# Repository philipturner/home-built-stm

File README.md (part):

## Members
Philip Turner, Nanoscience Student (2025)
philipturner@vt.edu

## Project Overview

> _Complexity is the nemesis of progress._

STM with no nonlinearities in the relationship between piezo voltage and position.

Presentation:
- [Video (YouTube)](https://www.youtube.com/watch?v=1APURT2G7bo)
- [Slides (PDF)](./Documentation/Presentation/Final%20Presentation.pdf)

Table of Contents:
- Journal Entries (Planning Stage)
  - [Progress (Jan 2025)](#progress-jan-2025)
  - [High-Level Overview](#high-level-overview)
  - [Lithium Niobate](#lithium-niobate)
  - [Finite Element Modeling](#finite-element-modeling)
  - [Chips](#chips)
  - [Update (February 22, 2025)](#update-february-22-2025)
  - [First Draft of TIA Subsystem](#first-draft-of-tia-subsystem)
  - [Bypassing vs. Decoupling Capacitors](#bypassing-vs-decoupling-capacitors)
- Journal Entries (Theoretical Stage)
  - [March 6, 2025](#march-6-2025)
  - [March 15, 2025](#march-15-2025)
  - [March 18, 2025](#march-18-2025)
  - [March 19, 2025](#march-19-2025)
  - [March 20, 2025](#march-20-2025)
  - [March 21, 2025](#march-21-2025)
  - [March 22, 2025](#march-22-2025)
  - [March 23, 2025](#march-23-2025)
  - [March 25, 2025](#march-25-2025)
  - [March 28, 2025](#march-28-2025)
  - [March 29, 2025](#march-29-2025)
  - [March 30, 2025](#march-30-2025)
  - [March 31, 2025](#march-31-2025)
  - [April 1, 2025](#april-1-2025)
  - [April 2, 2025](#april-2-2025)
- Journal Entries (Experimental Stage)
  - [April 6, 2025](#april-6-2025)
  - [April 7, 2025](#april-7-2025)
  - [April 8, 2025](#april-8-2025)
  - [April 9, 2025](#april-9-2025)
  - [April 10, 2025](#april-10-2025)
  - [April 11, 2025](#april-11-2025)
  - [April 12, 2025](#april-12-2025)
  - [April 13, 2025](#april-13-2025)
  - [April 14, 2025](#april-14-2025)
  - [April 15, 2025](#april-15-2025)
  - [April 16, 2025](#april-16-2025)
  - [April 17, 2025](#april-17-2025)
- Journal Entries (Conclusion Stage)
  - [April 18, 2025](#april-18-2025)
  - [April 22, 2025](#april-22-2025)
  - [April 25, 2025](#april-25-2025)
  - [May 5, 2025](#may-5-2025)
- Journal Entries (Experimental Stage, Revived)
  - [May 6, 2025](#may-6-2025)
  - [May 7, 2025](#may-7-2025)
  - [May 8, 2025](#may-8-2025)
  - [May 9, 2025](#may-9-2025)
  - [May 10, 2025](#may-10-2025)
  - [May 12, 2025](#may-12-2025)
  - [May 13, 2025](#may-13-2025)
  - [May 14, 2025](#may-14-2025)

## Progress (Jan 2025)

This project is officially a NANO 4994 research project for Spring 2025, worth 3 credits. After months of research, I found a potential solution to my main goal of building an STM, solving piezo creep. I discovered a new material that could make better piezoelectric actuators: <b>lithium niobate</b>. I am listing some of the calculations and scripts I have done. Currently, I am speed-running the tutorials for FreeCAD and KiCad. I have gotten through ~50% of them.

Small-scale studies and tests performed:
- [Charge Drives (Google Sheets)](https://docs.google.com/spreadsheets/d/1x5uQ4LPubufbuQAfBjDXJuyd1Wf3S6ZZu0C0zVwssfQ/edit?usp=sharing)
- [TemperatureSensor.swift](https://gist.github.com/philipturner/81bed277f2942c87ea8825910e91a766)
- [Accelerometer.swift](https://gist.github.com/philipturner/bb1920f50a6ece8943d76146afa0af87)
- [FourierTransformAcceleration.swift](https://gist.github.com/philipturner/d7ffa2e23931173a39b9624441069f12)
- [FourierTransformVelocityPosition.swift](https://gist.github.com/philipturner/a365d72c1ba5c4eedf1c331bb21d586d)
- [FrequencyResponse.swift](https://gist.github.com/philipturner/212ae83408707147ce6cd6f57adedc7e)
- [PiezoelectricCoefficients.swift](https://gist.github.com/philipturner/9fb9d81c1d2d1427b4287541a99e6cec)
- Ordered and received 10 lithium niobate piezo plates

I also read a few hundred pages of literature on:
- Nanopositioner design and control electronics
- Vibration isolation
- Ultra-high vacuum instrumentation and compatible technologies
- Ferroelectric materials (Landau Theory)
- A substantial portion of "Art of Electronics, 3rd Edition"

<b>Lithium is a high vapor pressure metal, just like zinc.</b> See [Vacuum Compatibility (Google Sheets)](https://docs.google.com/spreadsheets/d/1ahE9a9jptKb8CLytUUoq606xVC4pLZpgXXCualte69o/edit?usp=sharing). To carry this investigation to completion, I would need to validate that lithium niobate and conductive epoxy are UHV compatible. Or whatever else is used to solder SMT/SMD components in vacuum-compatible PCBs. Shear piezo stacks have been made before, and worked under 10^-11 torr backing pressures @ 300 K. It's just, the lithium in LiNbO3 evaporates more than the lead in Pb(Ti,Zr)O3. Liquid nitrogen should annihilate the vapor pressure during STM operation, but not during bakeout (likely the issue with high vapor-pressure metals). Might require longer bakeouts at lower temperatures.

The other downside: lithium niobate has a smaller piezo constant than PZT. About one tenth. In practical applications, compensating for the fact that LiNbO3 can withstand higher electric fields (higher voltages given fixed membrane width), the range is also one tenth. Except at cryo temperatures (liquid helium, 4 K) where the range is equal. But only if you stack 10-20 plates on top of each other. I am suffering two-fold from the loss of range. I can only afford to put in, maybe 2 piezo plates for any given actuator.

## High-Level Overview

The current high-level plan is very rough. It will be split into different modules, which can be constructed once and recycled multiple times. I will conduct multiple experiments in sequence, some of which will reuse this equipment. For example, the very first capacitance measurement experiment can use the same vibration isolator as a late-stage STM iteration. It could even opt to only use the interior isolation stage.

Sequence of experiments:
- Measuring capacitance change between two parallel plates, to verify piezoelectricity of LiNbO3
  - Using glass cover slides to enforce a pre-determined distance of ~300 μm. Then, verify that capacitance behavior matches the simulations.
    - Use the FreeCAD finite element simulator to model the capacitance, which needs corrections to the parallel plate model.
  - Verify the predicted behavior, that it shears in both X and Y.
- 1DOF scanning tunneling spectroscopy machine, that can maintain tunneling current without crashing the tip
  - 30 nm range single LiNbO3 plate, with 440 V effective (+/-110 V plus polarity reversal)
  - 3 nm coarse stepping size with Dan Berard style stepper motor stage, just 1 motor?
    - Although there is severe thermal drift, the handoff between fine Z range and coarse Z step might catch up
    - Otherwise, need to stack multiple piezo plates for Z. This is a topic of major importance.
  - Verify the measurement of 100 fA currents (100x more sensitive than the Mech Panda STM)
- 3DOF scanning tunneling microscope with limited range
  - 30 nm range on each axis, verified for the X/Y axes by counting number of HOPG unit cells.
  - Prove there is an absence of hysteresis and creep distorting the images of HOPG
  - Resolve individual atoms on Au(111), which Dan Berard could not do. Or find the reason it cannot be imaged under ambient conditions.
- Complete, end-goal iteration with 100 nm range X/Y/Z and vacuum compatibility
  - Remove the stepper motor Z coarse stage
  - Z fine actuator needs disproportionately more range (more LiNbO3 plates) to match the stepping size of the coarse stage
  - Add slip-stick/stick-slip inertial drive for X and Z axes, clamped by gravity
  - X coarse stage enables "tripod assembly line", reducing a sample swapping bottleneck during atom building
  - Coarse stage uses shear piezos, but potentially out of the inferior PZT just to increase their range
  - PZT has piezo creep, but it has a similar effect to thermal drift with stepper motors. Wait until the coarse stage settles.
- Ultra-high vacuum system at room temperature (far term development stage, beyond my work at Virginia Tech)
  - Prove that evaporation of lithium atoms from LiNbO3 is not a concern
  - Prove that evaporation of atoms from the conductive epoxy is not a concern
  - Prove that the system can withstand bakeout, if STM modules are typically required to undergo bakeout
  - Verify that the previously designed system can function (take an image) while producing a vapor pressure of under 10^-10 torr
 
Mechanical loop:
- The system modules are everything besides the tip-sample mechanical loop (which will change from experiment to experiment).
- The mechanical loop should be designed to have maximum resonance frequency.
- The mechanical loop should be designed to have minimum coefficient of thermal expansion.
- The electrical shielding should have minimum possible tip-ground parasitic capacitance (the limiter to current sensitivity).

System modules:
- UHV compatible spare pre-amplifiers
  - Each time a pre-amplifier is used, it might be soldered irreversibly to the STM tip
  - A custom design that minimizes parasitic capacitance, might need to be discarded with the broken tip
  - This is similar to qPlus sensors, which have some MEMS circuitry on whatever the tuning fork is glued to
  - Minimize the magnitude of thermal drift caused by the op-amp's ~7 mW power consumption
- Reversibly bondable piezo plates
  - Use magnets to make piezos reversibly stickable to something. You can stack them up, or instead distribute them across different axes (X/Y/Z).
  - Need to understand whether you can do this, without the magnetic force crushing the crystalline material.
  - Issues with isolating nearby circuitry (such as the grounded STM tip) from very high electric fields
- Two-stage spring suspension system
  - Viton high-frequency dampers are incompatible with UHV. They're compatible with HV, but not UHV (Viton has a vapor pressure of 10^-8 or 10^-7 torr).
  - Use a single-stage, compact spring for the high-frequency part. This is small enough to fit inside a UHV chamber.
  - Use a single-stage low-frequency isolator with ~1.7 Hz vertical resonance frequency. Copying the "Open STM" design.
  - The low-frequency isolator models a pessimistic outcome, where you need an air table, and you can't utilize Minus K technology.
  - This table would hold the entire UHV chamber in the far-term prototype. Near-term, it serves to conveniently hold the electronics.
- High-voltage amplification board (piezo driver board)
  - A large number (~5–10) of high-power op amps, with bipolar -110V / +110 V output ([ADHV4702-1](https://www.analog.com/en/products/adhv4702-1.html))
    - ["The industry's first 220 Vpp op amp"](https://www.analog.com/en/resources/design-notes/adhv4702-1-24-v-to-220-v-precision-operational-amplifier.html), invented in 2018.
    - There are 350 Vpp (-175 V / +175 V) designs out there, but they have triple the cost ($10 -> $28)
    - Might be more economical to use custom, discrete components to reach even higher voltages (Art of Electronics mentioned 0 V / +1 kV piezo driver)
  - Each LiNbO3 stack needs 2 dedicated op amps, so one electrode is +110 V while the other is -110 V. LiNbO3 can withstand extremely high electric fields.
  - Unused op amps should be turned off to reduce power consumption.
  - Might multiplex op-amps to the subset of piezoactuators in use at any moment.
  - Can be recycled for late-stage prototype with coarse piezoactuators under ambient conditions. Might keep one of the electrodes at GND for PZT plates, to avoid depoling them.
- Analog to digital board
  - [AD5761](https://www.analog.com/en/products/ad5761.html]) DACs with ~133 kHz bandwidth
    - Enough DACs to supply all the piezos that must be operated simultaneously, in the late-stage prototype (3 fine and 2 coarse, 5 total). Also, a DAC for the bias voltage.
    - High voltage setting: 20 Vpp range (-10 V / +10 V or 0 V / +20 V)
    - Low voltage setting: 6 Vpp range (-3 V / +3 V or 0 V / +5 V)
    - 16 bits, enough for picometer step size (the problem is increasing the range at the voltage peak; LiNbO3 has a small piezo constant)
    - DACs used as piezo drivers will be fed into the high-voltage amplification board, jumping from +/-10 V to +/-110 V (11 V/V amplification factor).
    - Analog Devices made some [open-source code](https://github.com/analogdevicesinc/no-OS/blob/main/drivers/dac/ad5761r/ad5761r.h) to operate this chip, which is nice.
  - [AD7746](https://www.analog.com/en/products/ad7746.html) CDC with 10-100 Hz bandwidth
    - "Capacitance to digital converter", fuses high-resolution capacitance detection circuitry with a 24-bit sigma-delta ADC
    - 10 Hz = 4 aF resolution
    - 100 Hz = 40 aF resolution
    - Accepts up to 4 pF variation range during dynamic operation, with 17 pF able to be accessed by a slow capacitance offsetting mechanism
    - The capacitance measurement setup in the paper that studied piezo creep, was 3.2 pF with 10 mm x 10 mm x 300 μm parallel plate capacitor
    - Removes the need for bulky, expensive "capacitance bridges" based on a four-element bridge with inductors and mechanical DACs (unsure how they work fully)
    - Useful to early-stage prototype measuring capacitance, and could serve as a sensor to aid in tip approach later on.
- Second half of TIA board
  - Processes the output of the pre-amplifier; this board doesn't need as much shielding
  - Complex analog circuitry for the 0.1 pA–50 nA, [fast low-noise transimpedance amplifier](https://pubs.aip.org/aip/rsi/article-abstract/91/7/074701/967357/Fast-low-noise-transimpedance-amplifier-for).
  - Contains the expensive (~$20–30) 18-bit ADC.
    - Plan to buy the low-bandwidth 250 kHz one. The way ADC bandwidths work, is they have either a fixed frequency or they are on sleep.
    - The analog part of this circuit has no more than 50 kHz (anything higher would have unacceptable e<sub>n</sub>C noise anyway).
    - No need to sample significantly higher than the true bandwidth.
  - Bandwidth switching circuitry and high-order filters, potentially multiplexing through a finite set of bandwidths.
    - Theoretical limit is the 50 fA bias current of the pre-amplifier.
    - Ultra low bandwidth (1-2 kHz, the circuit's natural corner frequency without correction) = 250 fA noise, mostly Johnson noise at 300 K
    - Low bandwidth (4.4 kHz) = 500 fA noise
    - High bandwidth (40 kHz) = 7 pA noise, mostly e<sub>n</sub>C noise
  - Current amplifier will not be needed for early capacitance testing experiments
- Power board
  - Accepts mains power (170 V amplitude AC power)
  - Three lines: +120 V, GND, -120 V
  - Third op amp in the fast low-noise TIA (+/-50 V output capability) can use a resistive voltage divider to supply rails with +/-60 V
  - Voltage divider for +/-20 V may or may not be implemented on the analog-to-digital board. Especially if the 18-bit ADC is migrated up there.
- Teensy 4.0 CPU
  - I don't need the extra memory of the 4.1. It's slower than main memory, so it's of no use anyway.
  - I don't need the extra ports of the 4.1, at least when counting the number of DAC lines and harnessing a few built-in ADCs.

Safety mechanisms for high-voltage electronics: major importance
- -110 V and +110 V away from electrical ground, or perhaps 220 V since the circuit's ground may float away from Earth.
- Anything above 40 V can generate a great enough electric field to break down human skin.
- It's often not the voltage, per se, that is the reason for danger (40 V is already way above the band gap of the toughest insulator).
  - Rather, it's the magnitude of the electric field, given the typical thicknesses of a thin film in context.
  - Also, high voltage generates high current, and the two multiply to give a high power through the human body.
- I'll reach up a bunch more, litter the PCB silkscreens with HV safety signs, add redundant mechanisms to physically prevent exposure to HV, etc.
  - I'm not an expert on HV safety yet, so the above precautions are not good enough to protect someone.

The plans above already need some revisions. Certain chips, such as the ADHV4702, are too expensive and must be replaced with a cheaper alternative. In addition, the piezo motor coarse approach mechanism is too expensive to fabricate, if one wants high stiffness. Instead, I am currently analyzing the common design for Air-STMs/EC-STMs, which uses electromagnetic motors. This is the design Dan Berard used.

## Lithium Niobate

Images of 10 lithium niobate plates that were delivered. Dimensions: 5 mm x 5 mm x 0.5 mm.

<p align="center">
&nbsp;
  
&nbsp; &nbsp;
  
&nbsp;
</p>

Crystallographic orientation:

## Finite Element Modeling

Source: https://dberard.com/2015/09/13/new-spm-design-progress

Image 1: Render from Dan Berard's CAD model, of his second prototype that was never built. Image 2: Cross-section of my FreeCAD model. Image 3: Finite element mesh created from the cross-section (29,955 nodes). Node count of the full STM model, without the cross-section, is 50,907.

<p align="center">
&nbsp;
  
&nbsp; &nbsp;
  
&nbsp; &nbsp;
  
&nbsp;
</p>

## Chips

The first iteration will avoid lithium niobate and high-voltage electronics. It will avoid the fast low-noise TIA design with an LTC6090-5 (140 Vpp) and opt for a simpler design with smaller dynamic range. Instead of 100 fA to 50 nA, it will target 200 fA to 10 nA. The output will go into an ADS8699 18-bit, 100 kHz ADC. I don't yet fully understand the requirements for LPF or differential pairs. The chip seems to include a 15 kHz second-order LPF within the IC (yet it has variants running SAR at 1 MHz?). I will have at least two bandwidths hard-coded into the hardware. The lower bandwidth will be ~5 kHz and require a custom LPF, regardless of the requirements for the high-bandwidth noisy mode. I would prefer a fourth-order Bessel filter, which seems optimal based on the graphs in Art of Electronics.

This prototype serves as a near-term experience, to get experience with constructing PCBs and precision analog electronics. It is a stepping stone toward a system with high-voltage electronics. The latter would require a custom voltage regulator and (potentially, in an even later prototype) custom high-voltage amplifier/piezo driver, with discrete transistor components. High voltages are needed because lithium niobate has a very small piezo constant. For example, extending 100 nm with 68 pm/V would require 1470 V. We can get around this slightly by stacking shear plates (only for XY actuators; Z-actuating LiNbO3 has major complications). But that only works to a certain extent. The cheap, in-stock LiNbO3 plates are relatively thick (0.5 mm). Physical dimensions must be kept <<10 mm per axis. We still have to employ high voltages (e.g. 294 V with 5 piezo plates per axis). The omission of HV electronics, for the first prototype, removes the high-voltage amplification stage (the DAC outputs drive the piezos directly). This lowers the complexity and cost.

The offset voltages for ADCs and DACs are non-trivial. However, based on skimming through some online stuff, trimming should be effective. The offsets supposedly stay constant with environmental conditions (temperature is the only thing that changes them? skeptical). DACs have a much greater offset voltage than ADCs. This is especially of note for the bias voltage. Scienta Omicron's overpriced STM has a lower bound to bias voltage dynamic range, of 5 mV. How do they perform sub-millivolt STS graphs? Maybe that instrument does not.

I still haven't tabulated all the chips needed. I likely won't have a Bill of Materials until I spend more time understanding transistors and discrete transistor feedback loop circuits. This is Art of Electronics chapters 2 and 3, some of the last ones I haven't read yet. Transistors are important for over-voltage regulators in the fast low-noise TIA design, so I need to understand how they work and what implications this has.

## Update (February 22, 2025)

This project is way out of scope for a single semester. I don't even want to make a 3D scanning STM first. I just want to solve the stability issue preventing people from taking quantitatively correct current-distance curves. Can I create a stable enough STM to measure the fact that current increases 10x every 80 pm, not 10x every Å? Thermal drift and piezo nonlinearities mean this cannot happen at 300 K. It has only been done at 4 K. I hypothesize that with a lithium niobate coarse approach mechanism, as outlined in [US12174218B2](https://patents.google.com/patent/US12174218B2), such a stability test will be possible at 300 K.

Here, I have recorded a snapshot of my current priority list. It is constantly under revision, as I answer questions. The answers to these questions result in even more questions appearing. The stable 1DOF nanopositioning system would be "Prototype 5". However, v5 is out of scope for a semester. Even v4 might be out of scope, due to the need for high-voltage electronics.

For Prototype 3:
- Find the best DAC chip
- First project:
  - Before next Tuesday, come back with a plan for this
  - Making a PCB that measures the values of resistors and capacitors

For Prototype 4:
- Learning about epoxy
- AoE x-Chapters part about inductors
- Understanding tilting and bowing in the capacitance sensor
- Understanding the reason for a sensor shaped like concentric cylinders
- Learning KiCad StepUp

For Prototype 5:
- Understanding the shear stress, and whether differences in polarization will break bonds in the frictional contact
- Calculate the critical amplitude for a coarse actuator design

To explain the current roadmap, I made a table. It lists the previous design iterations (1, 2) and the ones on my priority list.

| Prototype | Purpose |
| :-------: | ------- |
| 1         | First TIA on breadboard |
| 2         | Second TIA on breadboard, with ordered parts |
| 3         | Experience using the IC chips needed for the STM |
| 4         | Test rig for properly orienting piezo stacks |
| 5         | Stable 1DOF nanopositioner with kinematic mount |

There are technically 11 weeks between now and graduation. But more realistically, the budget is 9 weeks or less. I feel that, by putting these tasks on this project document, I might feel better. About crossing off a few of them, without taking the time to finish them. I can be more motivated to work on the near-term "Prototype 3" while also not forgetting the other tasks, in the future.

## First Draft of TIA Subsystem

<p align="center">
&nbsp;
  
&nbsp; &nbsp;
  
&nbsp;
</p>

## Update (February 26, 2025)

I will have to reduce the scope again. I still have the following questions:
- How does the successive approximation algorithm work?
- How does delta-sigma modulation work?
- What are the parasitics for the "capacitance bridge", and why was the 2550A supposedly better than the AD7746?

I am writing the questions on this document, hoping it will convince me to remove them from my TODO list (for now). I will remove the TIA, ADC, and CDC from the near-term initial prototype. Just the DAC remains. It will be powered by a battery (±5 V), and the output will be read with a multimeter.

I now only have the following questions left on my TODO list:
- Decide between the AD5761RBRUZ ([$14.49](https://www.mouser.com/ProductDetail/Analog-Devices/AD5761RBRUZ?qs=sGAEpiMZZMtgJDuTUz7Xu4AqHG%252BNl4bmQrNkJ2FPlwUUtx9Id5RwyQ%3D%3D)) and DAC81401 ([$13.23](https://www.mouser.com/ProductDetail/Texas-Instruments/DAC81401PWR?qs=mELouGlnn3e7ARpnyM2zAA%3D%3D)). Currently, the former appears to have better offset stability (unusually optimized around bipolar zero). The latter has better INL. Furthermore, the DAC8140x product line would readily facilitate future prototypes with multiple DAC channels.
- Understand what effects the instrumentation amplifier (bias voltage) or high-voltage amplifier (piezo driver) would have. Regarding offset, temperature drift of the offset, and temperature drift in general. These are chips that post-process the DAC's output. Their errors combine with the errors from the DAC.

## Bypassing vs. Decoupling Capacitors

I found a reference that demystifies the myriad capacitors sprouting out of ICs, and the inconsistency between example PCB layouts on datasheets. Source: https://designers-guide.org/design/bypassing.pdf

Next, I will:
- Understand the pins on the Teensy.
- Create a prototype PCB with the Teensy and the DAC.
- Perform "The Recipe" on the PCB traces.
- If I can get away with just a single 0.1 μF capacitor on each supply pin, I will do that.

## March 6, 2025

I reverted back to the original plan, of stuffing all three analog-to-digital ICs onto the near-term PCB. I am currently understanding the effects of parasitics, particularly "Header Sockets". These are parts that emulate the connections in breadboards. Header sockets allow reversible bonding of through-hole components as "devices under test". One can also reversibly connect different test points in the circuit, with jumper wires. Or interface them with a multimeter/oscilloscope. Such connections have a large amount of parasitic inductance.

I developed 8 different permutations of lumped element models, for simple "devices under test" between the DAC and the ADC. It starts with the parasitic output resistance of the DAC, 0.05 Ω. Then, it goes through a network of resistors, capacitors, and/or inductors (which may connect to GND). It ends with the parasitic input resistance of the ADC, 1 MΩ. I am using the SPICE functionality embedded in KiCad to understand the behavior of these parasitics. I previously invested well over 10 person-hours learning how to use KiCad's SPICE.
- 2 resistor geometries × 3 resistance values (1 Ω, 1 kΩ, 1 MΩ) = 6 permutations
- 2 short circuit geometries (THT with 1 cm jumper wire, SMT pads with 1 cm PCB trace)

I will put the following on this README:
- Screenshots of the KiCad schematic models
- Screenshots of the transient analysis (voltages and appropriate currents)
  - Units for time, voltage, and current in each transient analysis
- Screenshots of the AC small-signal analysis, for the DAC → ADC transfer function

Power source for transient analysis:

Power source for AC small-signal analysis:

To save time, I revised the number of models to 5. The first one is a simple test to get the hang of setting up simulations.

<details>
<summary>KiCad SPICE Models</summary>

| Device Under Test | Description | Model |
| ----------------- | ----------- | ----- |
| Circuit 1 | Simplified version of SMT short circuit |  |
| Circuit 2 | SMT short circuit from 1 cm PCB trace |  |
| Circuit 3 | THT resistor in header socket, 1 Ω |  |
| Circuit 4 | THT resistor in header socket, 1 kΩ |  |
| Circuit 5 | THT resistor in header socket, 1 MΩ |  |

</details>

<details>
<summary>Transient Analysis</summary>

| Device Under Test | V(Vout) | I(V2) |
| ----------------- | ------- | ----- |
| Circuit 1 | .jpg) | .jpg) |
| Circuit 2 | .jpg) | .jpg) |
| Circuit 3 | .jpg) | .jpg) |
| Circuit 4 | .jpg) | .jpg) |
| Circuit 5 | .jpg) | .jpg) |

</details>

<details>
<summary>AC Small-Signal Analysis</summary>

| Device Under Test | V(Vout) | I(V1) |
| ----------------- | ------- | ----- |
| Circuit 1 | .jpg) | .jpg) |
| Circuit 2 | .jpg) | .jpg) |
| Circuit 3 | .jpg) | .jpg) |
| Circuit 4 | .jpg) | .jpg) |
| Circuit 5 | .jpg) | .jpg) |

</details>

## March 15, 2025

To minimize the risk of running out of time, I will cut the AD7745 out of this project for now. It might be needed in the future, in the control electronics for a capacitive displacement sensor. That sensor's purpose is primarily to aid in testing LiNbO3 piezo stacks.

Instead, I plan to use the TIA to measure capacitance, with lock-in amplification. All good capacitance sensors use both an excitation signal and capacitance cancellation. The excitation signal can be a sine wave (AH2550A, TIA) or a square wave (AD7745). The cancellation capacitance reduces the magnitude of the background (unchanging) component of the capacitance. Without the cancellation capacitance, the large signal would saturate the sensor, or its shot noise would overbear the desired (small) signal.

There are three ways to implement a cancellation capacitance.
- <b>AD7745:</b> Excitation voltage stays the same, but value of capacitance values. There are 7-bit "CAPDACs" on each input terminal, which act effectively as negative capacitances.
- <b>AH2550A:</b> Wildly complex system using transformer taps. Switches between several physical capacitors, some as large as 1 μF.
- <b>TIA:</b> Fixed-value "compensation capacitor" attached to the terminal of the pre-amplifier. It receives the bias voltage, with opposite sign and gain of 0.1&ndash;10x.

The principal issues with the TIA are:
- Ensuring the leakage capacitor has very low leakage. A high-resistance material must be used. This is hard, as PTFE (a good material) is not UHV compatible. Instead, one could create an artificial vacuum capacitor. This has concerns of bulkiness (C ∝ size) and susceptibility to vibration (dC/dt × V looking like C × dV/dt).
- Ensuring the negated bias voltage's gain can vary. A mechanical trimpot is a bad idea in the long run, because when the tip approaches the sample, the background capacitance changes. The trimpot must be recalibrated. This can incur major human labor costs, in a factory with O(1000) scanning probes. Instead, one should use a digipot and incorporate gain switching into the coarse approach controller.

In <b>scanning capacitance microscopy</b>, people have reported ~1 aF sensitivity with a 1 V sine wave at ~100 kHz. This is a concern, as the ADS8699 has a low-pass filter at 15 kHz. I see no reason one cannot use a 10 V sine wave at ~10 kHz. The 1 V bias might have been due to the AFM tip already being close to the sample, and wanting to avoid large electrostatic forces. The purpose of capacitance sensing is to extract information about the tip-sample distance, when very far from the sample. I don't need it once tunneling is established.

Electrostatic shielding can reduce the magnitude of the background capacitance. This means the compensation capacitor can be smaller (it must be similar to the background capacitance in magnitude). It is also needed to reduce currents from radiofrequency interference. It may contribute to the parasitic capacitance (C<sub>in</sub>) that harms performance of the TIA.

In addition to capacitance measurement, a good TIA must have low leakage and interference currents. Here are some non-obvious notes regarding that.
- Leakage through a PCB (FR-4 material) might be non-negligible. In-vacuum transimpedance amplifiers are made of SMT components bonded to Macor. PCBs are not UHV compatible.
- Often, a PTFE standoff is used at the junction where tunneling current enters the op-amp. The IC pin may be pried off the PCB, and soldered to a wire going directly to the tip.
- In the case of qPlus AFM, the op amp is literally suspended in the air, held in place by wires reaching into its pins.
- The pre-amplifier stage should have a separate power supply, with very large capacitors. It is critical to suppress power supply noise, which can be a limiting factor to current sensitivity.

I'll have to judge what measures are feasible with the time remaining in this semester. I want a sensor with very high performance, that can be easily tested. The contacts for a "device under test" must be reversibly bondable. The testing system must be shielded.

Perhaps a model STM, with just two parallel plates moved together with a micrometer screw. It does not require vibration isolation, or automation of the coarse approach.

No, all of that is out of scope. Just have a PCB with a DAC and ADC. Include the TIA, but don't include shielding or leakage protection that would require a lot of effort.
- All test points are through-hole header sockets.
- I can cover the entire PCB with a construct of aluminum foil, for first-order shielding.
- The power supply is six 9V batteries, fed into a network of linear regulator ICs.
- The Teensy will bond directly to the PCB, via a carefully placed array of header sockets. No need for ribbon cables and intermediate boards between the Teensy and PCB.
- Separate ground plane for the Teensy (digital) and ADC/DAC SPI pins (analog). Each of the two chips has a quad-channel digital isolator (not an opto-isolator, but similar).

From the time budget in the February 22 update, I have effectively 6 weeks left. But Spring Break (the most productive week) is mostly over. The workload will get harder. I am participating in a group project, to plan and execute an organic synthesis. I will be very engaged, as it's invaluable to my future aspirations to synthesize tripods. Although that motivation has faded away; the even greater barrier might be time to construct a minimal-cost UHV SPM. Regardless, I have little time to waste.

## March 18, 2025

Correct control-loop model of the fast low-noise transimpedance amplifier:

<p align="center">
&nbsp;
  
&nbsp; &nbsp;
  
&nbsp;
</p>

Analysis, in progress at the time of writing:

[TransimpedanceAmplifierStability.swift](https://gist.github.com/philipturner/321f9a1ccf64319d583776371fe78bf2)

I could not use SPICE because the model for LTC6090-5 was closed-source. I could not trust the parameters for it. The other two amplifiers have open-source text files for SPICE, which are compatible with KiCad SPICE. The easiest way to understand "mid-f compensation" is actually to just script the transfer functions with Swift, and graph with Matplotlib. It is the second option after Wolfram Alpha stops working because I hit the character limit (the transfer function has too many variables).

Interestingly, I learned something about "LTspice" used in college electronics classes. It stands for "Linear Technologies SPICE". If you look at the app icon, it has the logo for Linear Technologies. The software IP transferred over to Analog Devices when they bought out LT. The buyout happened in 2016&ndash;2017. I realized the thing about LTspice after looking through old Internet Archive records, of the original company's website. The LTC6090/LTC6090-5 was released in 2013&ndash;2015.

<b>Update:</b> I think I figured this out. I can use KiCad SPICE to simulate the circuit. I just need to use the Swift script to verify the transfer functions for the single-pole approximations to each op-amp. Then, I'll reproduce each transfer function with a voltage-dependent voltage source + RC filter in SPICE. Verify that no feedback loop ever enters the region where the single-pole approximation is incorrect. This is >500 kHz for the OP37, >50 kHz for the LTC6090-5.

I don't have to worry about the incorrectness for LTC6090-5, as I won't use that chip in the real device. The inner feedback loops will likely be >500 kHz. But I'm not concerned about the moderately inaccurate phase shift for inner loops. Just that they are stable (which is pretty easy to guarantee). I care more about the detailed frequency response of the outer loop, which is far below 500 kHz. Therefore, I should be justified in parameterizing only a single-pole model. This saves time.

## March 19, 2025

I keep going back and forth about which tool I want to use. Generally, if I was not pressured for time, I would do everything custom. I only learned FreeCAD because there was an immense overhead to set up the geometry for finite element simulations. For electrical circuit simulations, the equations and algorithms are much simpler. In addition, scripting opens up the flexibility to explore more details, which are inaccessible from a UI-based program. Solving this problem with scripting would be a valuable experience, and prepare me to tackle future problems that existing tools can't address.

Finally!

## March 20, 2025

I have successfully created lumped-element models of the op-amps in KiCad SPICE, by referring to the code from the script. They reproduce the transfer functions shown above. I used voltage-controlled voltage sources to create unity-gain buffers, which prevent different filter sections from "loading" each other.

<i>Lumped-element model of the AD8615, configured for an AC small-signal analysis.</i>

I organized the KiCad project by creating multiple pages. One of the pages holds the models for the op-amps. There is text denoting which circuit is which op-amp model. This page is excluded from simulation. To set up a simulation, I can copy and paste the elements from this reference page, into the main page. This is similar to how I host reference code for MD simulations in a repository [(1)](https://github.com/philipturner/rod-logic) [(2)](https://github.com/philipturner/bootstrapping-code-archive), they copy it into an [Xcode project](https://github.com/philipturner/molecular-renderer) for customization.

The OP37G model has been translated <i>correctly</i>.

Another scope reduction: omit the ADC, DAC, Teensy, and optocouplers. We'll be using entirely analog input and analog/oscilloscope output methods. It is true, that going entirely analog makes the circuitry simpler. This a hard conclusion to reach, from someone who spent their entire previous career in the digital realm.

<b>Why is this true?</b> There are less questions about what is "ground", less need to isolate noisier grounds from quieter grounds. Another bonus, is you're not able to measure signals with 16-bit precision, so you don't have to optimize for low noise/drift. The total number of chips on the near-term prototype PCB is less. And the total number of decoupling and/or bypassing capacitors is less. Which means less time to set up the schematic, less time to place the components before soldering. Less traces on the PCB; op-amps and comparators have ~1/4 as many leads as ADC/DAC chips.

It's also easier to model, because the entire circuit (except the power supply and overvoltage protection) can be represented in the SPICE simulation. Everything is linearly dependent, given a fixed frequency. All the non-power pins and devices under test (impedances) can be described with linear algebra.

## March 21, 2025

I got the general structure of the custom design figured out. Instead of three inverting stages, there is one inverting stage (AD8615) followed by a noninverting stage (OP37G). This configuration is different from the problematic combination of a noninverting preamplifier with an inverting second stage. The frequency response should theoretically be identical to the amplifier from the fast low-noise TIA paper.

Response to a triangle wave + 1.0 pF device under test, after calibration. Note that the "mid-f compensation" appears to not affect the response when the current is a triangle wave. Only when the current is an infinitely sharp step. It eliminates the peaking that appears when input capacitance exceeds 90 pF and goes toward 95 pF, 130 pF.

Note that for this design, the second stage can be very sensitive to the parasitic capacitance between the terminals of OP2. If C<sub>in</sub> for OP1 is 130 pF, the circuit oscillates when C<sub>in</sub> for OP2 reaches ~350 pF. If C<sub>in</sub> for OP1 is 12 pF, the circuit oscillates when C<sub>in</sub> for OP2 reaches ~120 pF. This can be remedied by using tactics traditionally used for transmitting preamplifier input wires. Put the actual preamplifier in vacuum, and use what "once was" its 35 pF parasitic as the input capacitor for OP2. This ensures that (10 + 35 =) 45 pF < 120 pF.

## March 22, 2025

Capacitances that make the amplifier unstable. The tests are conducted when the "mid-f compensation" trimpot is at 25 kΩ, and the "main compensation" trimpot is tuned for a flat frequency response.

Custom design:

| OP1 C<sub>in</sub> | OP2 C<sub>in</sub> |
| -----------------: | -----------------: |
|   2 pF |  ≥ 26 pF |
|  12 pF | ≥ 121 pF |
|  45 pF | ≥ 264 pF |
| 130 pF | ≥ 370 pF |

Fast low-noise TIA:

| OP1 C<sub>in</sub> | OP2 C<sub>in</sub> | OP3 C<sub>in</sub> |
| -----------------: | -----------------: | -----------------: |
|   2 pF | unstable | unstable |
|   2 pF | unstable | unstable |
|   2 pF | unstable | unstable |
|  12 pF |  ≥ 50 pF |    10 pF |
|  12 pF |    10 pF |  ≥ 12 pF |
|  12 pF |  ≥ 12 pF |  ≥ 12 pF |
|  45 pF | ≥ 705 pF |    10 pF |
|  45 pF |    10 pF | ≥ 122 pF |
|  45 pF | ≥ 121 pF | ≥ 121 pF |
| 130 pF | ≥ 725 pF |    10 pF |
| 130 pF |    10 pF | ≥ 242 pF |
| 130 pF | ≥ 238 pF | ≥ 238 pF |

Tolerance for capacitance between terminals of post-amplifier stages:

| OP1 C<sub>in</sub> | OP2 C<sub>in</sub> (2-stage) | OP2 C<sub>in</sub> (3-stage) | OP3 C<sub>in</sub> (3-stage) |
| -----------------: | ------: | ------: | ------: |
|   2 pF |  ≤ 26 pF | unstable | unstable |
|  12 pF | ≤ 121 pF |  ≤ 50 pF |  ≤ 12 pF |
|  45 pF | ≤ 264 pF | ≤ 705 pF | ≤ 121 pF |
| 130 pF | ≤ 370 pF | ≤ 725 pF | ≤ 238 pF |

Interesting behavior with the three-stage design:
- When OP1 C<sub>in</sub> = 12 pF, reducing the "mid-f compensation" trimpot to 15 kΩ causes instability.
- When OP1 C<sub>in</sub> = 2 pF, the amplifier is always unstable. Even when the "mid-f compensation" trimpot is at 100 kΩ, and the resistance in series to C<sub>c</sub> is 1470 Ω.
- When OP1 C<sub>in</sub> = 45 pF, reducing the "mid-f compensation" trimpot to 15 kΩ does not cause instability.

Next, I must design an analog 2-stage lowpass filter that mimics the ADS8699's lowpass. It's important to include this test in the semester's project, as I likely won't actually test the ADS8699. The filter will not take much effort to include.

## March 23, 2025

Second-order lowpass filters to emulate the ADS8699 are out of scope. I need to figure out which voltage regulators to use. Also, I wonder how to/whether one should switch off the triangle wave generator.

Voltages required:
- AD8615
  - rail-to-rail input and output
  - no GND pin
  - positive supply: 2.5 V
  - negative supply: -1.5 V
  - If an input pin voltage exceeds the supplies, place resistor in series with the input, so that the current doesn't exceed 5 mA.
- OP37G
  - no GND pin
  - positive supply: 12 V to 18 V
  - negative supply: -12 V to -18 V
  - If differential input voltage exceeds 0.7 V, the input current should not exceed 25 mA.
- LM4040-10
  - 10 V reverse breakdown voltage between cathode and anode
  - tolerance in reverse breakdown voltage: 
    - ±10 mV (A grade)
    - ±20 mV (B grade)
    - ±50 mV (C grade)
    - ±100 mV (D grade)
  - 1 mA current change:
    - up to 1.5 mV voltage change (A, B, C grade)
    - up to 2.0 mV voltage change (D grade)
  - 15 mA current change:
    - up to 14 mV voltage change (A, B, C grade)
    - up to 18 mV voltage change (D grade)
- AD8676
  - rail-to-rail output
  - no GND pin
  - positive supply: 5 V to 18 V
  - negative supply: -5 V to -18 V
  - up to ±0.7 V input differential voltage tolerated
  - If power supplies are established awkwardly with respect to input signals, input current should not exceed 10 mA.
- TS861
  - rail-to-rail input
  - no GND pin
  - supply operation from 2.7 to 10 V
  - tolerates differential input voltages up to ±12 V (absolute maximum rating)

Currents required:
- AD8615
  - up to 2 mA quiescent supply current
  - output current:
    - up to 50 mA (2.7 V supply)
    - up to 150 mA (5 V supply)
- OP37G
  - total supply current:
    - 2.8 mA (24 V)
    - 3.1 mA (30 V)
    - 3.3 mA (36 V)
    - 5.7 mA (from 170 mW maximum at 30 V)
  - output current via maximum output voltage:
    - 1.5 mA (10 kΩ)
    - 4.8 mA (3 kΩ)
    - 14 mA (1 kΩ)
    - 37 mA (300 Ω)
    - 45 mA (200 Ω)
    - 50 mA (100 Ω)
  - For best linearity, the output current should not exceed ±10 mA.
- LM4040-10
  - recommended operating conditions: 0 to 15 mA
  - minimum cathode current:
    - up to 120 μA (A, B, C grade)
    - up to 130 μA (D grade)
  - example application: 4.7&ndash;10 kΩ resistance separating Zener from supplies
    - 4.7 kΩ, ±15 V: 1.1 mA
    - 4.7 kΩ, ±18 V: 1.7 mA
    - 10 kΩ, ±15 V: 0.5 mA
    - 10 kΩ, ±18 V: 0.8 mA
  - short-circuit "current": -39 mA to +45 mA
- AD8676
  - short-circuit "limit": +40 mA
  - output current: ±20 mA typical
  - supply current per amplifier:
    - up to 3.2 mA (±5 V supply)
    - up to 3.4 mA (±15 V supply)
  - ±50 μA output current used in the application
- TS861
  - supply current per comparator, output low:
    - up to 12 μA (2.7 V supply)
    - up to 12 μA (5 V supply)
    - up to 14 μA (10 V supply)
  - supply current per comparator, output high:
    - up to 14 μA (2.7 V supply)
    - up to 14 μA (5 V supply)
    - up to 16 μA (10 V supply)
  - Front page quotes 6 μA per comparator at 2.7 V supply.
  - Can source/sink up to 40 mA at 5 V supply. Likely higher at 10 V supply.

Summarize the information above:

| Chip | Voltage from (-) Supply to GND | Voltage from (+) Supply to GND | Quiescent Current from (+) to (-) Supply | Maximum Output Current |
| --------- | -----: | ----: | -------------------: | ------------: |
| AD8615    | -1.5 V | 2.5 V | 1.6&ndash;1.9 mA | 3 μA    |
| OP37G     |  -12 V |  12 V | 2.8&ndash;5.4 mA | 1.95 mA |
| OP37G     |  -15 V |  15 V | 3.1&ndash;5.7 mA | 1.95 mA |
| OP37G     |  -18 V |  18 V | 3.3&ndash;5.9 mA | 1.95 mA |
| LM4040D10 |    0 V |  10 V | 0.8&ndash;1.1 mA | n/a     |
| AD8676    |   -5 V |   5 V | 4.6&ndash;6.4 mA | 0.32 mA |
| AD8676    |  -10 V |  10 V | 5.0&ndash;6.6 mA | 0.32 mA |
| AD8676    |  -15 V |  15 V | 5.4&ndash;6.8 mA | 0.32 mA |
| TS861     |   -5 V |   5 V | 7&ndash;16 μA    | 0.32 mA |

Tradeoffs between supply voltages for OP37G. The difference in voltage noise is negligible.

| Supply Voltages | Open-Loop Gain | Common-Mode Range | Slew Rate, Falling | Slew Rate, Rising |
| --------------: | -------------: | ----------------: | -----------------: | ----------------: |
| ±12 V           | 1.6 million    | -9.5 V to 9.5 V   | -16.0 V/μs         | 17.0 V/μs         |
| ±15 V           | 1.8 million    |  -13 V to  13 V   | -17.0 V/μs         | 18.0 V/μs         |
| ±18 V           | 2.0 million    |  -16 V to  16 V   | -18.0 V/μs         | 18.5 V/μs         |

## March 25, 2025

The fight marches on. Only 4 weeks left. I will not fail to produce results this semester.

I spent a few days prying apart the voltage regulators. Created a 16-page Google Sheet.

[Voltage Regulators (Google Sheets)](https://docs.google.com/spreadsheets/d/1mhAkuCKq5BPGl8A8w-LUtCfJhjZLB09bPVywwgDxSec/edit?usp=sharing)

[VoltageDividerDesign.swift](https://gist.github.com/philipturner/36213b186f521f3313a14810f68e0b57)

I ended on investigating the voltage divider that creates +2.5 V and -1.5 V for the AD8615. If my computations are correct, one should use a pair of +5 V and -5 V voltage regulators. Not a pair of +15 V and -15 V regulators. And definitely not an LM317/LM337 pair.

I settled on a divider with three resistors, that touches the ground nowhere. Capacitors for AC stability/noise suppression were out of scope. I started investigating footprints for the SMT resistors, but realized that is an entire ordeal.

All of these capacitors, ground planes, ICs is out of scope. Capacitors grow out of the ICs like apples on a tree, placed haphazardly and sometimes not actually needed. One, two, or three ground planes make a cheap 2-layer PCB into an expensive 4-layer one. One of the 4 different regulated voltages gets to be king of its dedicated plane, the other 3 voltages don't.

I have a simple goal. A PCB with the 3 SMT resistors (357 Ω, 499 Ω, 806 Ω, 1% tolerance, 0603, Vishay) and 4 (isolated?) THT header sockets. No ground plane. But the solder paste footprints have the correct dimensions, as specified on Vishay's part datasheet. What specific width should the PCB traces have? That should be doable in 4 weeks of part-time work.

## March 28, 2025

The semester did not go as expected (there was no plan, really). I tried my hardest to build something related to the STM. I just lacked critical prerequisites in precision analog electronics and precision mechanical engineering. Stuff people might gloss over, and then build a device with inferior performance. I refuse to make anything other than the best possible hardware for a given set of constraints.

I will wrap the extensive computational and theoretical research on the transimpedance amplifier, into this semester's "deliverable." Likely not publishing a video about it (to save time, and there's not much to say) but instead a short PPTX to count for credit. Return to it in the far future, when I can work on it full-time.

| Event | Date | Time Until |
| ----- | ---- | ---------- |
| Today | 3-28-2025 | 0 days |
| Classes End | 5-7-2025 | 40 days |
| Graduation | 5-16-2025 | 49 days |
| Brief Return to Campus | 6-16-2025 | ~1 month after graduation |

I'm using the remaining weeks to gain valuable experience, on lab hardware I'll lose access to after graduation. The AMP lab has a reflow oven, decent hand soldering stations, oscilloscopes, CNC machining, etc. I'll get a very simple PCB designed, ordered, and soldered. Learn how to place the SMT components and operate the reflow oven myself. Then, learn how to operate the "high-end" CNC machine with G-code generated in FreeCAD.

| Accessible Now | Alternative at Home Lab |
| -------------- | ----------------------- |
| Reflow oven | Sand bath in a frying pan |
| Oscilloscope | Custom mixed-signal DAQ boards |
| CNC machine | Online CNC services |
| - | Two-component epoxy systems |
| Sputtering | Electrochemical deposition |

Simultaneously, I'm trying very hard to get gold sputtered onto a silicon wafer. Not the $1,000 gold samples you can order, but being in the same room when the sputtering is taking place. I do not foresee having access to UHV equipment until the very far future. I'll try to build it myself, and avoid sample preparation processes that require explosive gases. There's a half-possible chance I can build diamond-like spaghetti carbon (only C and H atoms) in a garage lab, without moving out to a dedicated lab building. Or at least hydrogen depassivation lithography. Depends on whether I can do without an argon ion gun (literal particle accelerator) and XPS sensor. And the timing/logistics of germa-adamantane tripods.

[Demonstration of mechanosynthesis with only carbon dimers on pre-charged germanium tooltips](https://www.youtube.com/watch?v=whvXCeEwlmI)

I need the flexibility to do graduate school full-time, without the bureaucracy and restrictions associated with a graduate degree. Being able to work full-time in a personal lab like [NileRed](https://www.youtube.com/@NileRed/videos). Until that happens, even a "simple" piezo stack with lithium niobate is out of scope.

No time to waste! There is work to do.

## March 29, 2025

Why is it so hard and complicated to specify a printed circuit board for manufacturing? There are at least 20 different parameters relevant to the process. And OSH Park, what I thought was the best service, doesn't ship steel stencils. You have to defer that to OSH Stencils. Other manufacturers (PCBWay, JLCPCB) might bundle stencils with your order. You need steel stencils to apply solder paste in a way other than randomly "dabbing" a "bit" on each precison pad.

OSH Park won't accept `.kicad_pcb` files from KiCad 9; they need files from KiCad 8. I find these practical implementation issues amusing.

## March 30, 2025

A few random notes (don't know where to put them):
- The issue with lithium and vacuum compatibility is still a concern. Its vapor pressure falls between zinc and lead. Perhaps baking out at a lower temperature (400 K instead of 500&ndash;800 K), for a longer time, will be needed.
- I don't want to have to wash parts in a bath of boiling trichloroethylene. This step might be an unscientific method for cleaning UHV parts.
- Wear a face mask while handling UHV parts, so you don't sneeze and add a layer of filmic contaminant.

## March 31, 2025

Helpful note. In the KiCad PCB editor, change all silkscreen items to be 0.635 mm x 0.127 mm. It allows the text to match the manufacturing tolerance of OSH Park. In the board setup constraints, set:
- Minimum item clearance: 0.127 mm
- Minimum text height: 0 mm
- Minimum text thickness: 0.127 mm

## April 1, 2025

Rule: Keep the symbols as close as possible to a generic chip,
no special op amp symbols or special linear regulator symbols.
Prefer the Snapeda symbols.
- Link datasheet and price to library symbol.

Rule: Use a standard set of footprints derived from the
KiCad library. Link them to the symbols, which are unique
for each part model.
- Delete the unique footprints and 3D models to reduce file size.

Avoid open-frame potentiometers.

Valid series (single-turn):
- 3313/3314/PVG3 ($1.23)
- 3329/3345/PV32
- 3361 ($1.10)
- 3362/3386 ($0.56)

Valid series (multi-turn):
- 3005/3006/3009/3057/3059/3082 ($1.79)
- 3214/3224/PVG5 ($2.44)
- 3223
- 3250/3252/3260/3262/3266/PV37 ($2.23)
- 3269
- 3290/3292/3296/3299/PV36 ($1.53)
- 3339/PV12

## April 2, 2025

I found myself having an unexpected few days with a few hours of free time. I used it to make another attempt at the transimpedance amplifier. I went through another design iteration of fixing problems with setting up the KiCad project. Made custom symbols and footprints for the ~12 different ICs.

I was preparing to set up the last dozen distinct circuit components. I got stuck on the enormous combinatorial space for trimming potentiometer types, and read a few dozen pages in a potentiometer handbook. I only got halfway through a Google Sheet characterizing the entire product catalog for Bourns trimpots.

Since final exams are coming up, I will likely not have another large block of free time like this. Or if I do, it's too risky to invest it into finishing the TIA. I can put the TIA to the side, and have it be the first thing I return to after graduation.

I must spend as much of this remaining time as possible:
- Getting experience with assembling mixed-technology PCBs
- Getting experience with CNC machining
- Attempting to get experience with a vacuum system capable of 10^-8 torr (10^-9 torr on a very good day)

## April 6, 2025

So I finally broke ground with real hardware. I did reflow soldering. Next, I am working on setting up an appointment to learn advanced hand soldering. I added 36 JPG images to the repository, with no effort to reduce data footprint. So the amount of data jumped 43 MB, dwarfing previous efforts to minimize disk consumption. Oh well, caught up in the moment.

I followed some online Environmental Health and Safety modules and applied for swipe access to the AMP Lab. If granted, it would let me work on the CNC machine on my own schedule, just like my style for fixing the AFM last semester. Go into the lab every day, spending hours, without waiting on other people's schedule conflicts to restrict how much time I can spend. Schedule conflicts are the reason I have to wait until at least next week to make further progress on soldering.

The lab has a Denford 2600 / 2600 Pro CNC router. There are two main categories of 3-axis CNC machines for general-purpose 3D shaping. Routers and mills. Routers are less mechanically stable, and for machining softer materials like wood. Luckily, routers can machine the softest metals (6061 aluminum and brass) with the right tools and techniques. I can across an interesting realization about Dan Berard's aluminum blocks. He didn't use a CNC machine, but instead hand tools from a machine shop. That poses questions about what geometry can be CNC machined, such as the V-grooves. V-grooves might be important for kinematic mounts in my future STM design iterations. Worth looking into.

I found another unexpected bout of free time. Internal conflict: continue work on the spreadsheet about potentiometers, or read the Denford 2600 manual. What to do while waiting for the ability to access the machine, and download the manual on the lab's PC. Looks like some new homework came in, so I'll work on that instead. Question answered.

Some explanation of something else that was going on behind the scenes recently. Someone who was too easily discouraged by the pains of real-world hardware work. Claimed that my entire effort should not receive funding, because it's doomed to fail. That, even if lithium niobate improves the speed of SPMs, they're still not fast enough to build a replicator. I harshly ended that argument by declaring that I'll start a company, build a semiconductor fab with O(1000) scanning probes, and start the next industrial revolution. _You're taking the argument too far. Didn't mean it that serious. Chill out._ I can use words and video editing as a weapon too, and I have more experience with both. From here on out, I'm not diluting the fact that I'm going for APM (atomically precise _mass_-manufacturing). Even if it makes me sound crazy, it's a matter of survival and securing funding. Nothing shall stand in my way, now that I've torn down CBN's idea that they hold leverage over the intellectual property for inverted mode mechanosynthesis.

That motivated me to spend ~20 person-hours solving the "Drake Equation" for how much it costs to bootstrap a replicator. The end result, so soundly crushed the argument that SPMs are too slow, I started obsessing about the next fundamental theoretical problem (where do we go from here; what's next?). About getting an atomically detailed design of a self-replicator, so we can reduce the atom count estimate to something under 200 million atoms. There's not much intellectually rigorous theory out there about replicator atom count, besides [Kinematic Self-Replicating Machines (2004)](https://www.molecularassembler.com/KSRM.htm). It has been renamed "exponential assembly" and "factory pixels", and some well-deserving low-level technical ideas. But there was no indication of how many DOFs the compact atom builder would have, and its complete atom count. Even if it's made of spiroligomers, there's a fundamental minimum bound to the number of building blocks required to make a mechanical system complex enough to do 3DOF actuation. Atoms or spiroligomers, all indications are that we cannot place building blocks faster than a few 100 Hz per macroscale atom builder working in parallel. At this point, the only difference between carbon dimers vs. spiroligomers/amino acids/DNA base pairs/other polymer units, is one requires high vacuum and the other doesn't. Which changes the cost maybe a factor of 3, not a factor of 1 trillion.

[CostEstimates.md](https://gist.github.com/philipturner/8d1d6680932b01fae4700b6f20da5198)

Enough theory. It's distracting. _Really_ distracting. It resurrected my desire to make a CAD program capable of handling ~64 million atoms in real-time. I had quit the computational and theoretical side because I felt there was competition from MSEP. No purpose working in an already saturated field. Now, I see that there's not actually competition there. I also switched sides because I got insider information about CBN's experimental progress. Was super unhappy that they weren't telling anybody about it. Now, I've destroyed their veil of secrecy over Twitter (in the heat of the moment due to frustration one day). And I'm confident they cannot fabricate LiNbO3 piezo stacks to fix their bottleneck. So I don't see a threat from competition on the experimental side. <ins><b>_Very dangerous train of thought._</b></ins> The competition still exists, they're still building atoms and not telling anybody. But at least I'm writing about that on this document, instead of Twitter (which I'm making an effort to quit).

How one question about theoretical SPM atom placement speed, can nearly derail my experimental effort. I'm still reeling, trying to suppress the heart-wrenching feeling of sacrificing my desire to render millions of atoms. Giving up on a hobby I've had for years, optimizing GPU code. Feels like playing Minecraft, which I had to give up once. I've worked so hard to build an experimental toolset, learn KiCad and FreeCAD. To put myself in the best position to make progress on experiment. That breakthrough, doing real-world reflow soldering on real-world hardware. It was the first step, and now I'm finishing up getting back the motivation to be 100% experimental. Piezo creep doesn't care what my desires are. It continues to plague SPM as we speak. It's the reason we're 30 years in and nanobots still don't exist.

Real-world hardware is so much more difficult than theory, or commentating on experimental efforts you're not participating in yourself. More difficult than holding meetings and attempting to convince investors with fancy PPTX's. Nobody's going to give you money. DARPA won't, frankly because you don't have a deliverable that can be implemented in an engineering blueprint. Where is the FreeCAD model of the facility with 1000 scanning probes? I'll quit today's lab journal entry while I'm at it...

## April 7, 2025

Swipe access granted.

Today, I answered some more fundamental questions about the control electronics. We need 2 DAC channels for the bias voltage. One for the primary bias, and another for the negative-polarity bias to cancel the capacitive current. The cancellation capacitor can have a nonzero conductance. We can detect and subtract this unwanted resistive current in software, because it's 90° out of phase from the capacitive current. In addition, the magnitude of the resistive current stays constant, even as the frequency of the sinewave changes. Having 2 different DAC channels solves the issue of dynamically altering the magnitude of the negative-polarity bias sinewave. It also solves the issue of the two polarities being out of phase/having a large time offset, because now they will go through the same analog low-pass filter, with ideally the same phase shift/time delay.

<ins><b>_I will build 1 singular atom in a repeatable programmable way, 1 atom in isolation._</b></ins> That was my whole goal since Oct. 2024 and it has not changed. The main goal is not to hire employees, give other aspiring people the ability to physically access my lab, build a self-replicator, or liquefy hydrogen. I just want to substantiate my [mechanosynthesis simulations](https://github.com/philipturner/mechanosynthetic-build-sequences) with a real-world experiment. That has always been my goal. Nobody can take away my funding. I went _too far_ perhaps in an effort to ensure the funding goes to direct-path SPMs, and not to incremental-path floppy proteins. Suppressed the notion that incremental path is the way to molecular nanotechnology. Side note, should tone down the rhetoric about CBN from now on, it's not going to help me build a vacuum system.

I might be close to figuring out the most accessible chemistry. Energetically, it goes downhill from Ge-C to Si-C. But it also goes downhill from Ge-C to W-C. Possibly moreso than silicon. This makes it more convenient to do mechanosynthesis (given a situation where you've already folded on HV and accepted the undesired fate of fabricating a UHV system). More convenient because you can just use a W wire instead of a degenerately doped Si cantilever (the latter conducts poor STM current). Also, perhaps you can MBE thiol tripods onto an Au surface, instead of depositing them in solution? To get better control over ensuring they're spaced out 100 nm between each molecule. Either that, or maybe conventional-mode mechanosynthesis (dense monolayers with 1 nm spacing between molecules) could be more accessible at 10^-6 torr? 10^-6 to 10^-9 torr is exponentially more accessible than 10^-10 torr to 10^-12 torr.

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
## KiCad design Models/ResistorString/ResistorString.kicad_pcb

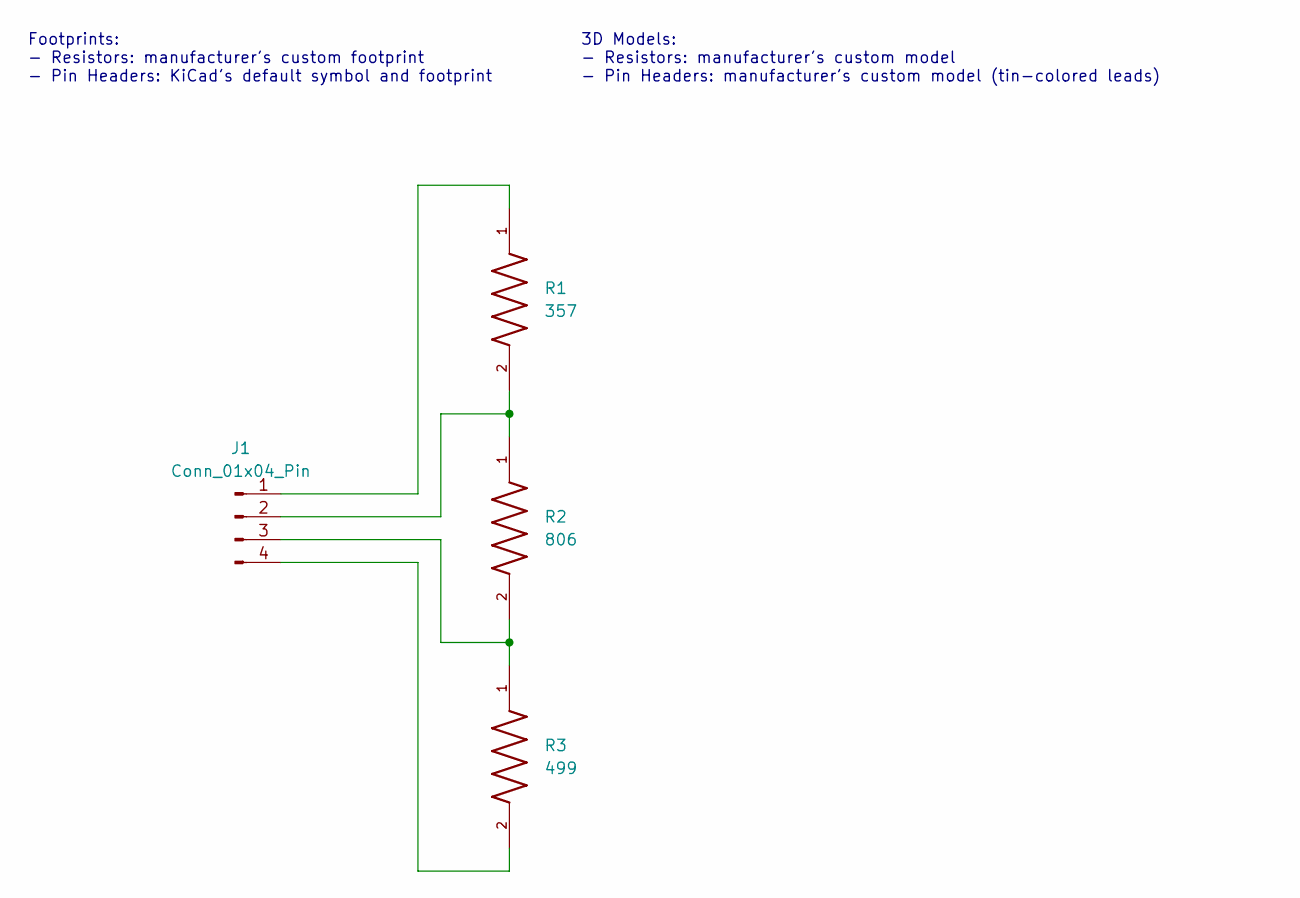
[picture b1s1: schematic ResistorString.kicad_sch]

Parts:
J1: Conn_01x04_Pin; PinHeader_1x04_P2.54mm_Vertical
R1: 357; RESC1508X50N
R2: 806; RESC1508X50N
R3: 499; RESC1508X50N

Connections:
unnamed: J1.1, R1.1
unnamed: J1.2, R1.2, R2.1
unnamed: J1.3, R2.2, R3.1
unnamed: J1.4, R3.2

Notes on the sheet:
Footprints: - Resistors: manufacturer's custom footprint - Pin Headers: KiCad's default symbol and footprint
3D Models: - Resistors: manufacturer's custom model - Pin Headers: manufacturer's custom model (tin-colored leads)

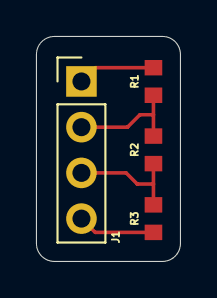
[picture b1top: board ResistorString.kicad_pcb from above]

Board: 2 copper layers, 8.0 x 12.5 mm, 4 parts (0 on the bottom side), 4 nets.

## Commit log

2024-10-25 Adding more description
2024-10-25 Removing unnecessary files
2024-10-25 Add resources
2024-10-26 Removed the EasyEDA files. EasyEDA is an unusable application and unusable software vendor in general.
2025-01-15 Add project update
2025-01-15 Add a description of what I did since the repo was created
2025-01-21 Rename the images
2025-01-27 Added the FreeCAD model of the Dan Berard STM
2025-01-29 Add screenshot from simulation
2025-01-30 Upload most recent version of Dan Berard v2 FCStd
2025-02-02 Typo fix
2025-02-22 Project update
2025-02-24 Push first draft of TIA subsystem
2025-02-24 Attempting to reformat
2025-03-02 Formatting fix
2025-03-09 Add screenshots of power sources
2025-03-09 Change the power circuits
2025-03-09 Added first image, see how the formatting goes
2025-03-10 See whether this table looks okay
2025-03-10 This should look better
2025-03-10 Reduce the number of images that must be taken
2025-03-10 Added the second model
2025-03-10 Added the third circuit
2025-03-10 Added the fourth circuit
2025-03-10 Upload KiCad project for this analysis
2025-03-10 Added the fifth circuit
2025-03-15 Spelling corrections
2025-03-15 Fix typo
2025-03-16 Scanning Capacitance Microscopy!
2025-03-16 Fixed several typos
2025-03-18 Document progress on understanding the TIA
2025-03-19 Will do the heavy lifting in SPICE instead of scripting, to save time setting up the simulation
2025-03-19 Going back and forth about what's the best option
2025-03-20 Post the graph of the parameterized transfer functions
2025-03-20 Update the graph
2025-03-20 Workable method to simulate the TIA in KiCad
2025-03-20 Upload the KiCad project
2025-03-20 Add the Bode plot of the OP37G
2025-03-20 A realization about analog/linear electronics
2025-03-20 Upload completed model of the LTC6090-5
2025-03-21 Upload latest version of TIA stability KiCad project
2025-03-21 Upload KiCad project with fully developed model of TIA from the paper
2025-03-22 Finally came up with a modification to the fast low-noise TIA
2025-03-22 Warning about design downside
2025-03-22 Add investigation into parasitic input capacitances
2025-03-23 Add observations for the AD8676 chip
2025-03-23 Add observations for the TS861 chip
2025-03-23 Let's see how this table looks on the README
2025-03-23 Add data for different supply voltages for OP37
2025-03-23 Added some information to the table
2025-03-23 Fix the formatting
2025-03-23 Another attempt at fixing the formatting
2025-03-23 Add the output currents to the table
2025-03-25 Started a KiCad project for an easy deliverable
2025-03-25 One more specification to list
2025-03-28 Final weeks of the project?
2025-03-29 Complaint about how hard this is in practice
2025-03-29 Upload modified KiCad project
2025-03-31 Reminder about setting up the PCB layout
2025-04-01 Upload new KiCad project for transimpedance amplifier
2025-04-01 Added KiCad libraries for more chips
2025-04-01 Massive cleanup to the libraries for the transimpedance amplifier
2025-04-01 Some notes about potentiometers
2025-04-02 See whether this commit works
2025-04-02 Commit some more images
2025-04-02 Added some more images
2025-04-06 Add update about the CNC machine
2025-04-06 Lab journal entry
2025-04-06 Attempt to fix formatting issue
2025-04-06 Attempt to fix formatting issue again
2025-04-07 First day doing hand soldering
2025-04-08 Every day, some more of the motivation returns
2025-04-08 Made a correctly functioning piece of real-world hardware, for the first time in a long time
2025-04-08 Reminder of the time left, the new trajectory this project is taking
2025-04-09 Add images for CNC machining
2025-04-09 Skeleton of the journal entry
2025-04-09 Add some of the images now
2025-04-09 Rewording
2025-04-09 Fix up the last image at a later time
2025-04-09 Calibrated the display sizes of the two uneven images
2025-04-09 Final lab notes for today
2025-04-11 Lab notes for yesterday
2025-04-11 Remark about the Bath Of Boiling Trichloroethylene
2025-04-11 Finished today's entry
2025-04-13 See whether the formatting is right for the dropdown
2025-04-13 Some formatting corrections
2025-04-13 Wrote this to build up the motivation to work on something else
2025-04-14 Started today's journal entry and added the table of contents
2025-04-14 Added measurements of the jig
2025-04-14 Added another note to the journal entry
2025-04-14 Added note
2025-04-14 Figuring out the type of apex termination
2025-04-14 Added image of the software window
2025-04-15 Added today's lab images
2025-04-15 Add link to the YouTube video
2025-04-15 Final notes for today's entry
2025-04-16 Started today's entry
2025-04-16 Rest of today's journal entry
2025-04-16 Good news about the gold sputtering sub-project
2025-04-22 Insights about the venture into the past
2025-04-22 Added more to the table of contents
2025-04-22 Resolve after this experience
2025-04-22 More thinking
2025-04-25 Another entry
2025-04-25 Another comment
2025-04-26 Added images of the CNC machine from today's meeting
2025-04-26 Upload the images for sputtering
2025-04-26 Finally upload the lab notes and images, after carefully specifying that the lab is not accessible to students
2025-05-02 Preparing for publication
2025-05-05 Add YouTube link
2025-05-07 Add the May 5 journal entry
2025-05-07 Upload the latest lab images
2025-05-07 Add the May 6 journal entry
2025-05-07 Added some more media
2025-05-07 Note to self
2025-05-07 Completion of today's journal entry
2025-05-07 This formatting for the captions looks better
2025-05-08 Some formatting cleanups for the project page
2025-05-08 Start of today's journal entry
2025-05-08 Upload the raw notes for the journal entry
2025-05-08 Upload today's images, group 1
2025-05-08 Upload today's images, group 2
2025-05-08 Revise the instructions for the note to self
2025-05-08 Formatted the first 2 images
2025-05-08 Added some more images. Good time to review how they look on the public repository.
2025-05-08 Added another two images
2025-05-08 This image was uploaded in too high of a resolution
2025-05-08 Save progress and add the remaining unsorted notes
2025-05-08 Finished uploading the images. Going to add labels to the image of desoldered components.
2025-05-08 Modified the image to include labels
2025-05-08 Cleaned up the lab notes some more
2025-05-08 I don't need AI
2025-05-09 Upload today's lab data
2025-05-10 Added some of today's images and organized JiviBoard into its own folder
2025-05-10 Added the raw notes for today's entry, and sorted the last few sessions into their own region of time
2025-05-10 Cleaned up the formatting of the raw text
2025-05-10 Upload the first set of images
2025-05-10 Upload the second set of images
2025-05-10 Formatted the images about the tombstoned capacitor
2025-05-10 How does this table appear?
2025-05-10 Does this fix the table?
2025-05-10 Tweaking the image width a little more
2025-05-10 Formatted some more images
2025-05-10 Reword this for clarity
2025-05-10 Formatted the last of the images
2025-05-12 Started today's journal entry
2025-05-12 Added clarification to the first paragraph
2025-05-12 Rationale for the new parameters for feeds and speeds
2025-05-12 Preparing to upload media of the 3rd test of CNC machining
2025-05-12 Check how these media look on GitHub
2025-05-12 Outlined some starting goals for today's session
2025-05-12 Measured the amount of space left via the mechanical calipers + set another goal to make this session more complete
2025-05-12 Observations about the removed material
2025-05-12 More proper phrasing
2025-05-12 Update on how the dust was removed
2025-05-12 About to film a video
2025-05-12 Might have more ambitious goals than previously outlined
2025-05-12 Clarify the last sentence
2025-05-12 The previously planned tasks are done
2025-05-12 Placed the video link in chronological order of when it was filmed
2025-05-13 Documented what I currently know about the drill bits
2025-05-13 The rigging has been taken care of
2025-05-13 Listed the factors that might break a tool
2025-05-13 Going to exchange drill bits before trying anything
2025-05-13 Note about slotting
2025-05-13 First steps toward figuring out the correct feeds and speeds
2025-05-13 Gathered internet data about feeds and speeds
2025-05-13 Posted the raw data
2025-05-13 Decision for feeds and speeds
2025-05-13 Added just the notes, will upload the media in a separate commit
2025-05-13 Going to try again, and hopefully get good results
2025-05-13 Observed what actually happened in the last operation
2025-05-13 Last test. Needs further investigation.
2025-05-14 Beginning of today's journal entry
2025-05-14 Uploaded the media
2025-05-14 Reported all of the observations
2025-05-14 Conclusions about what to try next
2025-05-14 First bits of investigation into chatter
2025-05-14 Reword this
2025-05-14 Added an observation from a Breaking Taps video
2025-05-14 Another observation about spindle speed
2025-05-14 Plan for testing
2025-05-14 See how the table looks with this formatting
2025-05-14 Adjusting the table's formatting
2025-05-14 Observations for the next test
2025-05-14 Observations for these next two tests
2025-05-14 Results of the test with 4000 RPM
2025-05-14 False alarm about damage to the drill bit
2025-05-14 Note about X axis calibration
2025-05-14 Observations for the 5000 RPM test
2025-05-14 Make the last few tests more conservative, don't want to risk needing to exchange the bit, which would take time
2025-05-14 Back to the parameters used for milling wood
2025-05-14 Results for the 7000 RPM test
2025-05-14 Observations for the 8000 RPM test
2025-05-14 Next steps for this lab session
2025-05-14 Reword the sentence
2025-05-14 Uploaded image of the results
2025-05-14 Moving on to the next test
2025-05-14 Success at milling multiple passes without breaking anything
2025-05-14 Results of the latest test are more promising
2025-05-14 Addendum to the next plans
2025-05-14 Comments on the latest test
2025-05-14 Notes after seeing the results of example12
2025-05-14 Upload the media, not fully formatting to save time
2025-05-14 Added the last media besides the video
2025-05-14 Cleaned up the captions
2025-05-14 Use more uniform word choice
2025-05-14 This order seems more appropriate
2025-05-14 Avoid confusion with drill bits
2025-05-14 Add the link to the video
